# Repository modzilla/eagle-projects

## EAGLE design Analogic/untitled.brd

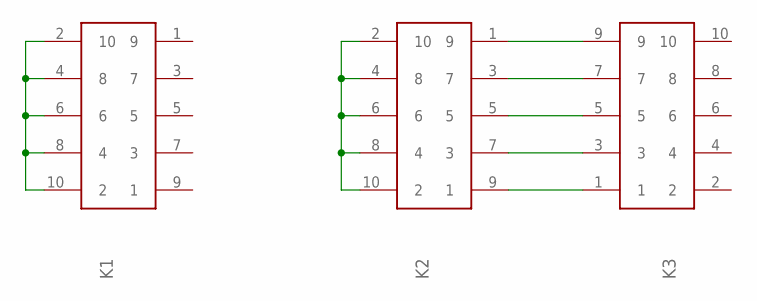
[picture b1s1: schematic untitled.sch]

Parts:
K1, K2: 61201021721
K3: 612X1020621

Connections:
unnamed: K2.9 (1), K3.1
unnamed: K2.7 (3), K3.3
unnamed: K2.5, K3.5
unnamed: K2.3 (7), K3.7
unnamed: K2.1 (9), K3.9
unnamed: K2.2 (10), K2.4 (8), K2.6, K2.8 (4), K2.10 (2)
unnamed: K1.2 (10), K1.4 (8), K1.6, K1.8 (4), K1.10 (2)

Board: 2 copper layers, 3 parts (0 on the bottom side), 7 nets, no tracks yet.

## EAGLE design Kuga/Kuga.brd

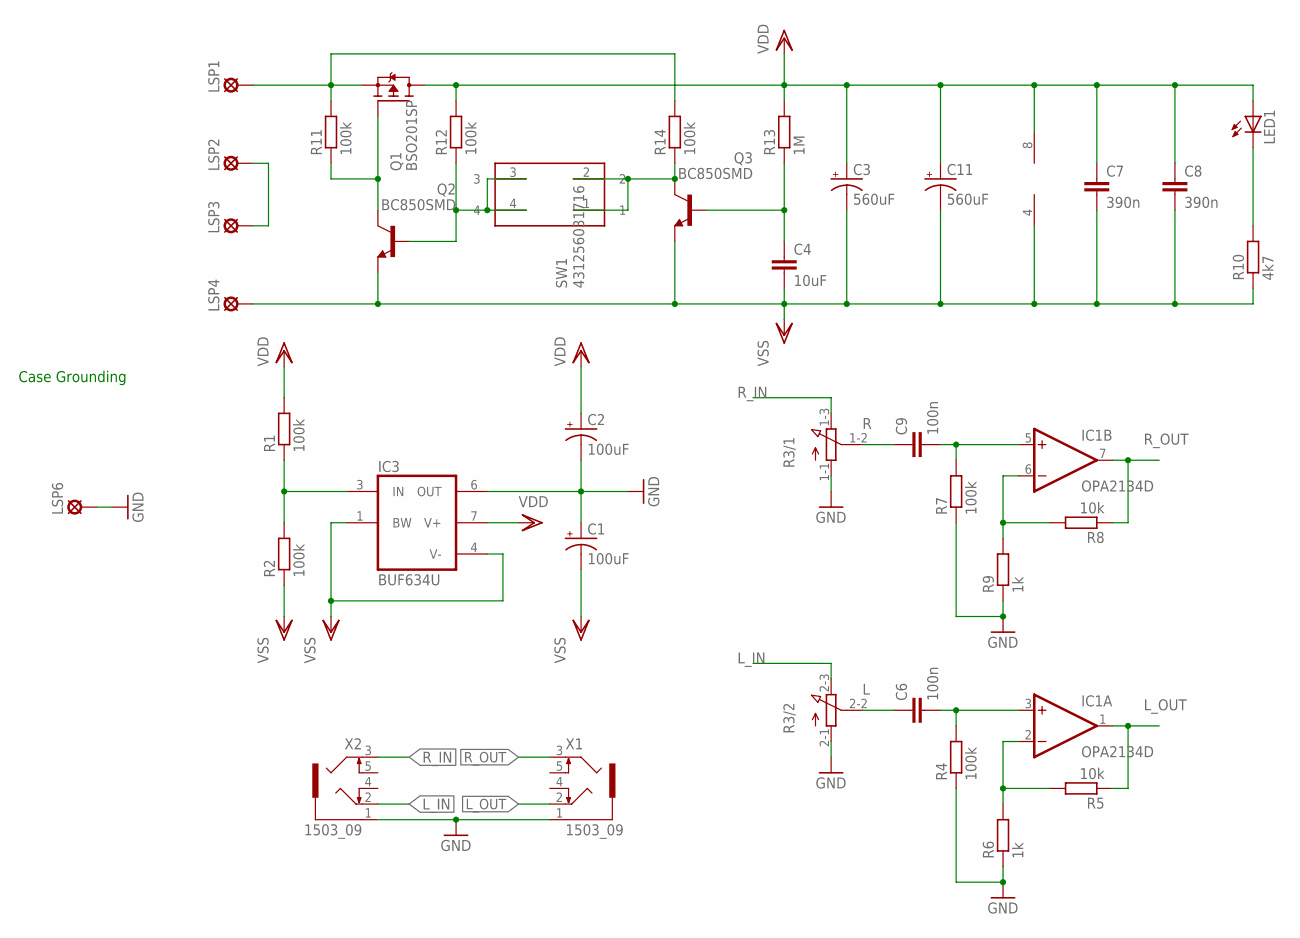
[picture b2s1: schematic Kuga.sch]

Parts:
C1, C2: 100uF; PANASONIC_D
C3, C11: 560uF; PANASONIC_G
C4: 10uF; 1210
C6, C9: 100n; C1206
C7, C8: 390n; C1206
IC1: OPA2134D; SOIC8
IC3: BUF634U; SO08
LED1: LED3MM
LSP1, LSP2, LSP3, LSP4, LSP6: LSP10
Q1: BSO201SP; SO-8
Q2, Q3: BC850SMD; SOT23-BEC
R1, R2, R4, R7, R11, R12, R14: 100k; R1206
R3: 3RP/1610G
R5, R8: 10k; R1206
R6, R9: 1k; R1206
R10: 4k7; R1206
R13: 1M; R1206
SW1: 431256031716
X1, X2: 1503_09

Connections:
GND: C1.+, C2.-, IC3.6 (OUT), LSP6.MP, R3.1-1 (A), R3.2-1 (A), R4.1, R6.1, R7.1, R9.1, X1.1, X2.1
L: C6.1, R3.2-2 (S)
L_IN: R3.2-3 (E), X2.2
L_OUT: IC1.1 (OUT), R5.1, X1.2
unnamed: LED1.K (C), R10.2
unnamed: C6.2, IC1.3 (+IN), R4.2
unnamed: IC1.2 (-IN), R5.2, R6.2
unnamed: C9.2, IC1.5 (+IN), R7.2
unnamed: IC3.3 (IN), R1.1, R2.2
unnamed: IC1.6 (-IN), R8.2, R9.2
unnamed: LSP1.MP, Q1.1 (S), Q1.2 (S), Q1.3 (S), R11.2, R14.2
unnamed: Q2.B, R12.1, SW1.3, SW1.4
unnamed: Q1.4 (G), Q2.C, R11.1
unnamed: C4.1, Q3.B, R13.1
unnamed: Q3.C, R14.1, SW1.1, SW1.2
R: C9.1, R3.1-2 (S)
R_IN: R3.1-3 (E), X2.3
R_OUT: IC1.7 (OUT), R8.1, X1.3
VDD: C2.+, C3.+, C7.1, C8.1, C11.+, IC1.8 (V+), IC3.7 (V+), LED1.A, Q1.5 (D), Q1.6 (D), Q1.7 (D), Q1.8 (D), R1.2, R12.2, R13.2
VSS: C1.-, C3.-, C4.2, C7.2, C8.2, C11.-, IC1.4 (V-), IC3.1 (BW), IC3.4 (V-), LSP4.MP, Q2.E, Q3.E, R2.1, R10.1
~BAT: LSP2.MP, LSP3.MP

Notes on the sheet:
Case Grounding

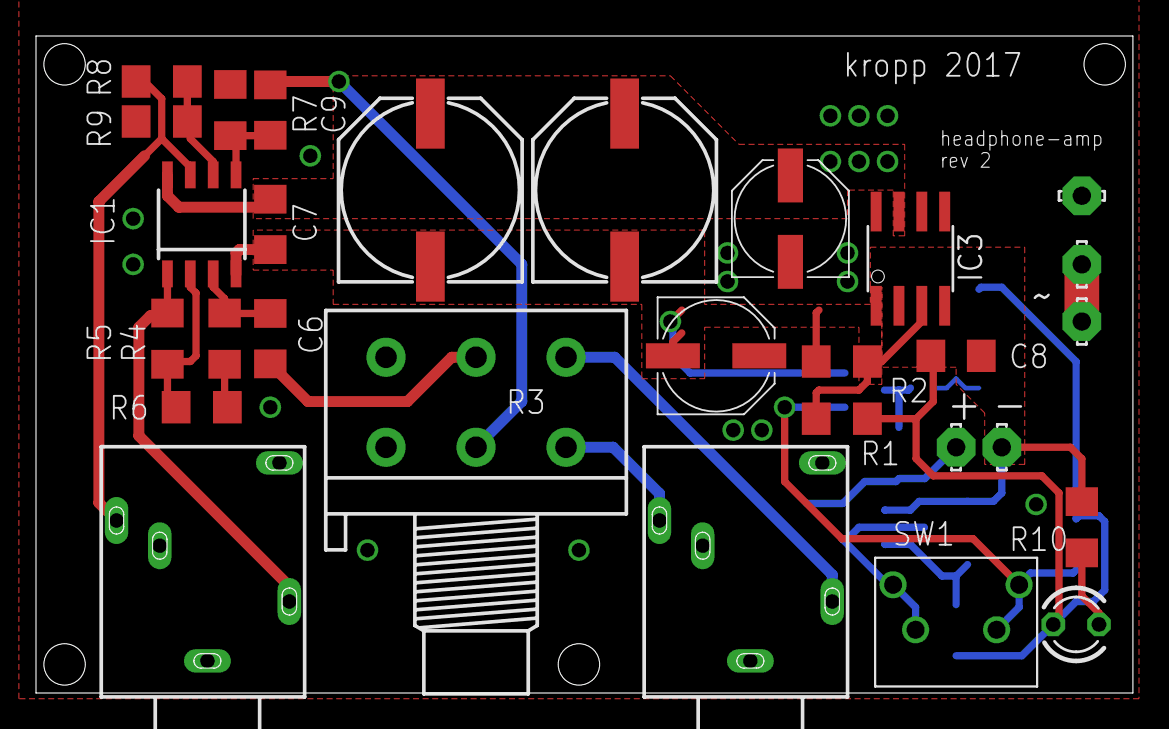
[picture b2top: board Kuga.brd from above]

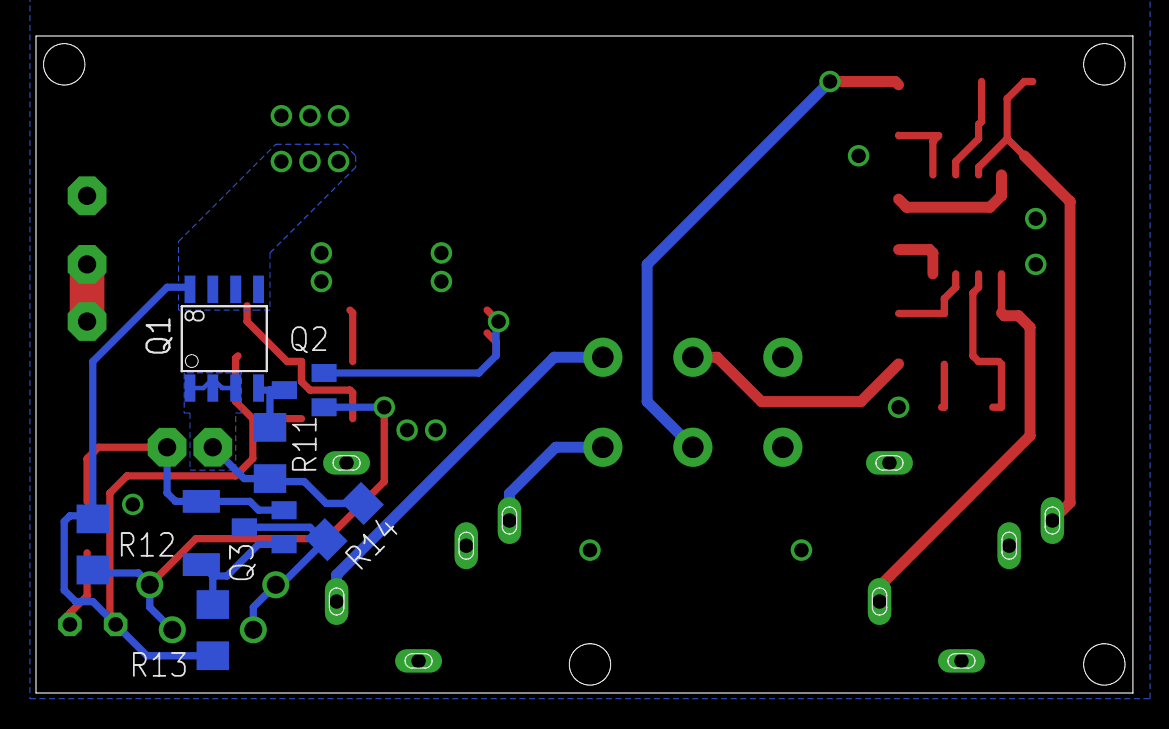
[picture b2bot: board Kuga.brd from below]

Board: 2 copper layers, 60.9 x 36.5 mm, 37 parts (8 on the bottom side), 21 nets.

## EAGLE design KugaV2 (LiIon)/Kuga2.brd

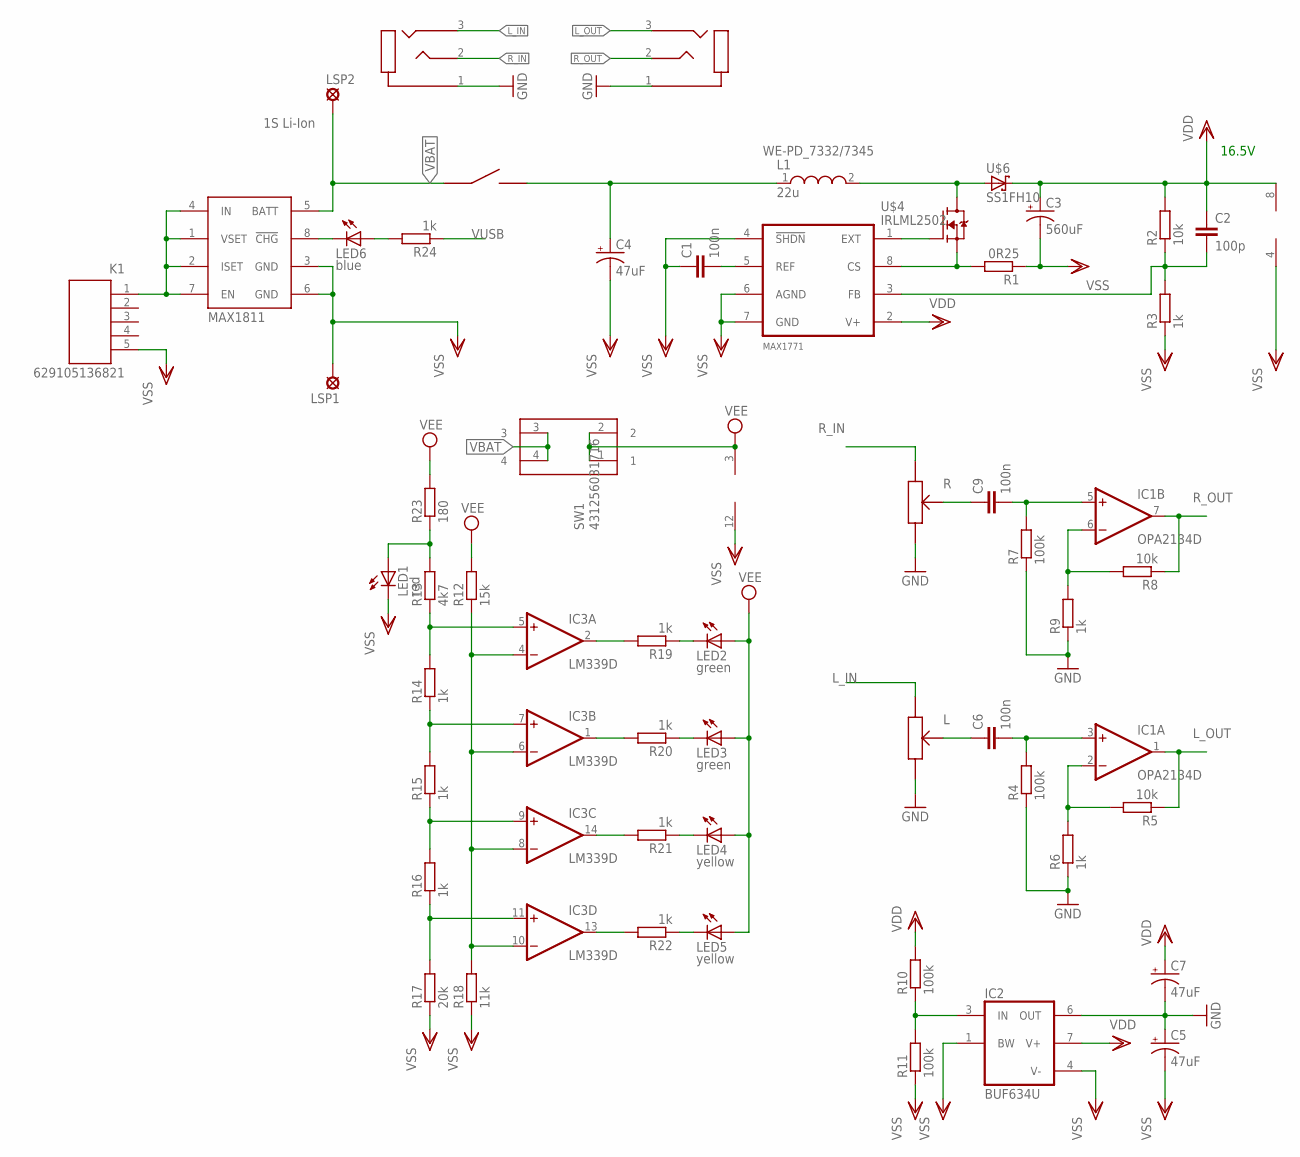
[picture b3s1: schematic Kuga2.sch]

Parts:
C1: 100n; C0603K
C2: 100p; C0603
C3: 560uF; PANASONIC_G
C4, C5, C7: 47uF; PANASONIC_D
C6, C9: 100n; C1206
IC1: OPA2134D; SOIC8
IC2: BUF634U; SO08
IC3: LM339D; SO14
K1: 629105136821
L1: 22u; WE-PD_7332/7345
LED1: red; CHIP-LED0603
LED2, LED3: green; CHIP-LED0603
LED4, LED5: yellow; CHIP-LED0603
LED6: blue; CHIP-LED0603
LSP1, LSP2: LSP10
MAX1771: MAX1771; SO-08
MAX1811: MAX1811; SO-08
R1: 0R25; M3216
R2: 10k; R0603
R3, R14, R15, R16, R19, R20, R21, R22, R24: 1k; R0603
R4, R7: 100k; R1206
R5, R8: 10k; R1206
R6, R9: 1k; R1206
R10, R11: 100k; R0603
R12: 15k; R0603
R13: 4k7; R0603
R17: 20k; R0603
R18: 11k; R0603
R23: 180; R0603
SW1: 431256031716
U$1, U$2: SJ1-3515-SMT-TR; STX-35332-3N-TR
U$4: IRLML2502; SOT23
U$5: PTR90; PTR902
U$6: SS1FH10; DO-219AB

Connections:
GND: C5.+, C7.-, IC2.6 (OUT), R4.1, R6.1, R7.1, R9.1, U$1.1 (SLEEVE), U$2.1 (SLEEVE), U$5.R13 (13), U$5.R23 (13)
L: C6.1, U$5.R22 (12)
L_IN: U$2.3 (RING), U$5.R21 (11)
L_OUT: IC1.1 (OUT), R5.1, U$1.3 (RING)
unnamed: IC2.3 (IN), R10.1, R11.2
unnamed: C6.2, IC1.3 (+IN), R4.2
unnamed: IC1.2 (-IN), R5.2, R6.2
unnamed: C9.2, IC1.5 (+IN), R7.2
unnamed: MAX1771.8 (CS), R1.2, U$4.2 (S)
unnamed: IC1.6 (-IN), R8.2, R9.2
unnamed: MAX1771.1 (EXT), U$4.1 (G)
unnamed: L1.2, U$4.3 (D), U$6.A
unnamed: LED6.C, MAX1811.8 (!CHG)
unnamed: LED6.A, R24.2
unnamed: IC3.4 (-IN), IC3.6 (-IN), IC3.8 (-IN), IC3.10 (-IN), R12.1, R18.2
unnamed: C2.2, MAX1771.3 (FB), R2.1, R3.2
unnamed: IC3.5 (+IN), R13.1, R14.2
unnamed: C1.2, MAX1771.5 (REF)
unnamed: IC3.7 (+IN), R14.1, R15.2
unnamed: IC3.11 (+IN), R16.1, R17.2
unnamed: IC3.9 (+IN), R15.1, R16.2
unnamed: IC3.2 (OUT), R19.2
unnamed: IC3.1 (OUT), R20.2
unnamed: IC3.14 (OUT), R21.2
unnamed: IC3.13 (OUT), R22.2
unnamed: LED2.C, R19.1
unnamed: LED3.C, R20.1
unnamed: LED4.C, R21.1
unnamed: LED5.C, R22.1
unnamed: LED1.A, R13.2, R23.1
R: C9.1, U$5.R12 (12)
R_IN: U$2.2 (TIP), U$5.R11 (11)
R_OUT: IC1.7 (OUT), R8.1, U$1.2 (TIP)
VBAT: LSP2.MP, MAX1811.5 (BATT), SW1.3, SW1.4, U$5.SW1 (11)
VBATSW: C4.+, L1.1, U$5.SW2 (12)
VDD: C2.1, C3.+, C7.+, IC1.8 (V+), IC2.7 (V+), MAX1771.2 (V+), R2.2, R10.2, U$6.K (C)
VEE: IC3.3 (V+), LED2.A, LED3.A, LED4.A, LED5.A, R12.2, R23.2, SW1.1, SW1.2
VSS: C1.1, C3.-, C4.-, C5.-, IC1.4 (V-), IC2.1 (BW), IC2.4 (V-), IC3.12 (GND), K1.5, LED1.C, LSP1.MP, MAX1771.4 (!SHDN), MAX1771.6 (AGND), MAX1771.7 (GND), MAX1811.3 (GND), MAX1811.6 (GND), R1.1, R3.1, R11.1, R17.1, R18.1
VUSB: K1.1, MAX1811.1 (VSET), MAX1811.2 (ISET), MAX1811.4 (IN), MAX1811.7 (EN), R24.1

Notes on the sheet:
16.5V
1S Li-Ion
WE-PD_7332/7345

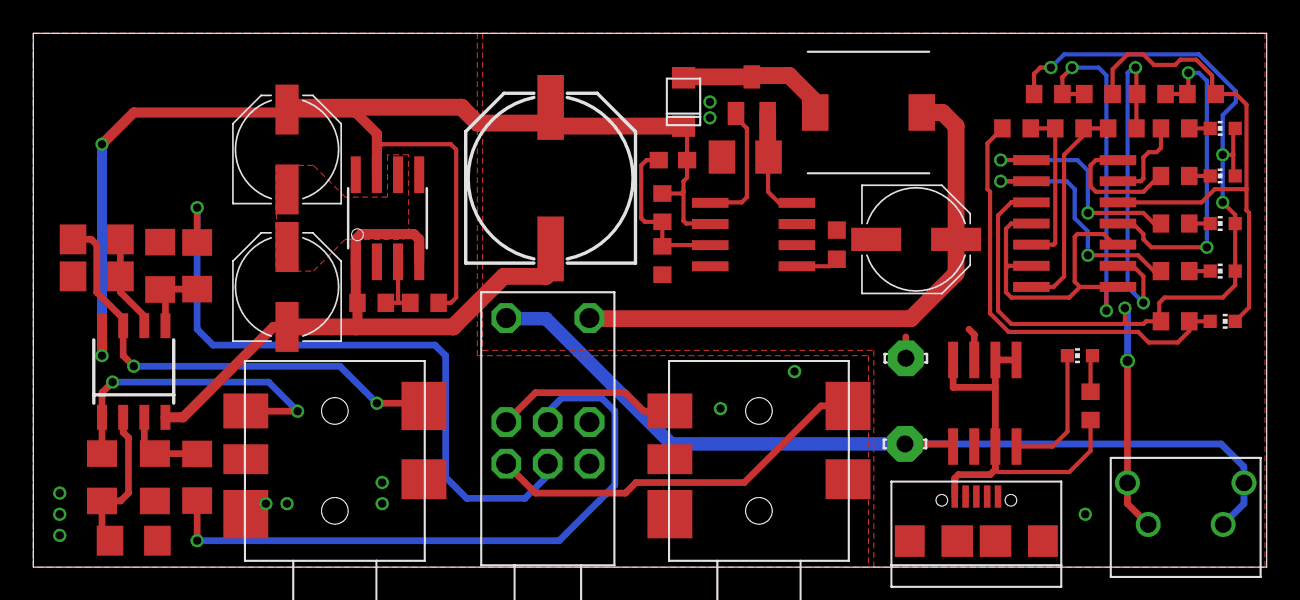
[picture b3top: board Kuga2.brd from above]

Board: 2 copper layers, 74.1 x 32.1 mm, 53 parts (0 on the bottom side), 39 nets.

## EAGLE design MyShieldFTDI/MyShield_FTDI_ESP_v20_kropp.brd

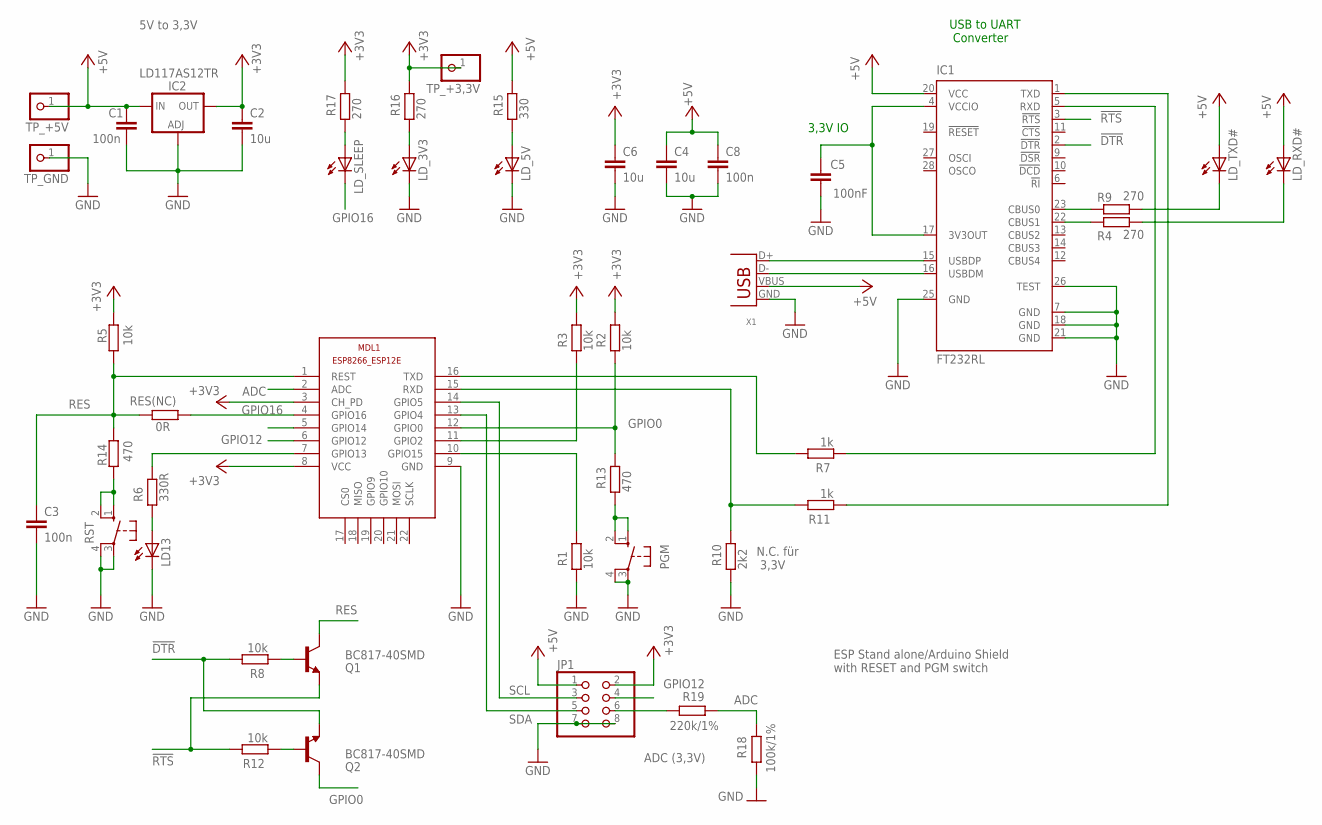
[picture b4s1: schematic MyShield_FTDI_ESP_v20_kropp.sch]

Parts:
C1, C3, C8: 100n; C1206
C2, C4, C6: 10u; C1206
C5: 100nF; C1206
IC1: FT232RL; SSOP28
IC2: LD117AS12TR; SOT223
JP1: PINHD-2X4; 2X04
LD13: LEDSMT1206; 1206
LD_3V3, LD_5V: LEDSMT1206; 1206
LD_RXD#: LEDSMT1206; 1206
LD_SLEEP: LEDSMT1206; 1206
LD_TXD#: LEDSMT1206; 1206
MDL1: ESP8266-12EESP8266-ESP12E; ESP8266-ESP12E
PGM: 10-XX; B3F-10XX
Q1, Q2: BC817-40SMD; SOT23-BEC
R1, R2, R3, R5, R8, R12: 10k; R1206
R4, R9, R16, R17: 270; R1206
R6: 330R; R1206
R7, R11: 1k; R1206
R10: 2k2; R1206
R13, R14: 470; R1206
R15: 330; R1206
R18: 100k/1%; R1206
R19: 220k/1%; R1206
RES(NC): 0R; R0805
RST: 10-XX; B3F-10XX
TP_+3,3V, TP_+5V: PINHD-1X1; 1X01
TP_GND: PINHD-1X1; 1X01
X1: USB-A-S

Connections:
3V3OUT: C5.2, IC1.4 (VCCIO), IC1.17 (3V3OUT)
!DTR: IC1.2 (!DTR), Q2.E, R8.2
!RTS: IC1.3 (!RTS), Q1.E, R12.2
+3V3: C2.1, C6.1, IC2.4 (OUT), JP1.2, MDL1.3 (CH_PD), MDL1.8 (VCC), R2.2, R3.2, R5.1, R16.2, R17.2, TP_+3,3V.1
+5V: C1.1, C4.1, C8.1, IC1.20 (VCC), IC2.3 (IN), JP1.1, LD_RXD#.A, LD_TXD#.A, R15.2, TP_+5V.1, X1.VBUS
ADC: MDL1.2 (ADC), R18.1, R19.2
GND: C1.2, C2.2, C3.2, C4.2, C5.1, C6.2, C8.2, IC1.7 (GND), IC1.18 (GND), IC1.21 (GND), IC1.25 (GND), IC1.26 (TEST), IC2.1 (ADJ), JP1.7, JP1.8, LD13.C, LD_3V3.C, LD_5V.C, MDL1.9 (GND), PGM.3, PGM.4 (P1), R1.1, R10.1, R18.2, RST.3, RST.4 (P1), TP_GND.1, X1.GND
GPIO0: MDL1.12 (GPIO0), Q2.C, R2.1, R13.2
GPIO12: JP1.4, MDL1.6 (GPIO12)
GPIO16: LD_SLEEP.C, MDL1.4 (GPIO16), RES(NC).1
unnamed: MDL1.7 (GPIO13), R6.1
unnamed: LD13.A, R6.2
unnamed: LD_TXD#.C, R9.2
unnamed: LD_RXD#.C, R4.2
unnamed: IC1.23 (CBUS0), R9.1
unnamed: IC1.22 (CBUS1), R4.1
unnamed: IC1.16 (USBDM), X1.D-
unnamed: JP1.6, R19.1
unnamed: Q1.B, R8.1
unnamed: IC1.15 (USBDP), X1.D+
unnamed: LD_SLEEP.A, R17.1
unnamed: MDL1.10 (GPIO15), R1.2
unnamed: MDL1.11 (GPIO2), R3.1
unnamed: Q2.B, R12.1
unnamed: PGM.1 (S), PGM.2 (S1), R13.1
unnamed: R14.2, RST.1 (S), RST.2 (S1)
unnamed: LD_3V3.A, R16.1
unnamed: LD_5V.A, R15.1
RES: C3.1, MDL1.1 (REST), Q1.C, R5.2, R14.1, RES(NC).2
RX_UA: IC1.5 (RXD), R7.1
RX_UA2: MDL1.16 (TXD), R7.2
SCL: JP1.3, MDL1.14 (GPIO5)
SDA: JP1.5, MDL1.13 (GPIO4)
TX_UA: IC1.1 (TXD), R11.1
TX_UA2: MDL1.15 (RXD), R10.2, R11.2

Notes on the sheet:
5V to 3,3V
ESP Stand alone/Arduino Shield with RESET and PGM switch
3,3V IO
USB to UART Converter
N.C. für 3,3V
ADC (3,3V)

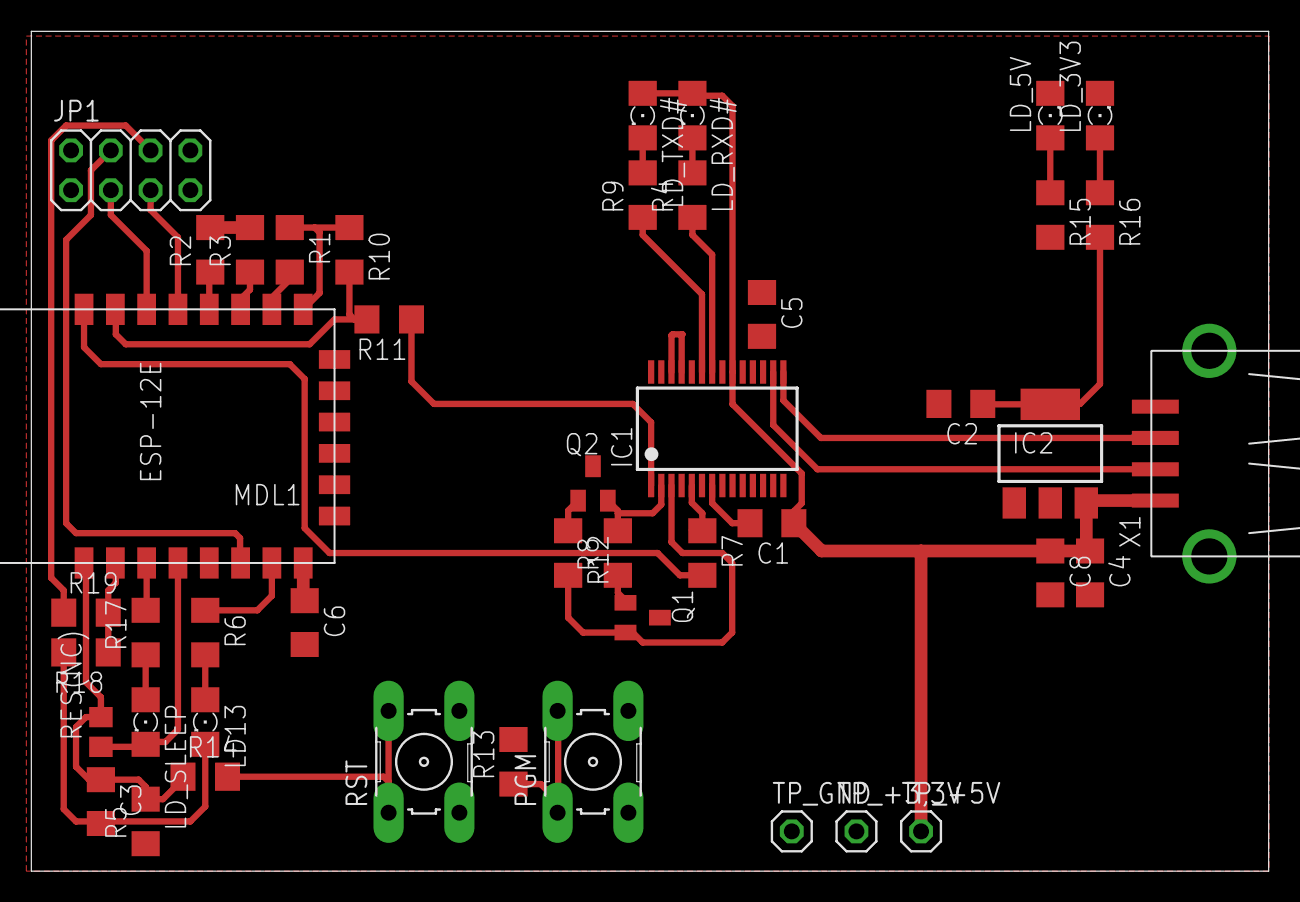
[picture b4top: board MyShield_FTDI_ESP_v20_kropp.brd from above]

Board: 2 copper layers, 79.0 x 53.6 mm, 45 parts (0 on the bottom side), 35 nets.

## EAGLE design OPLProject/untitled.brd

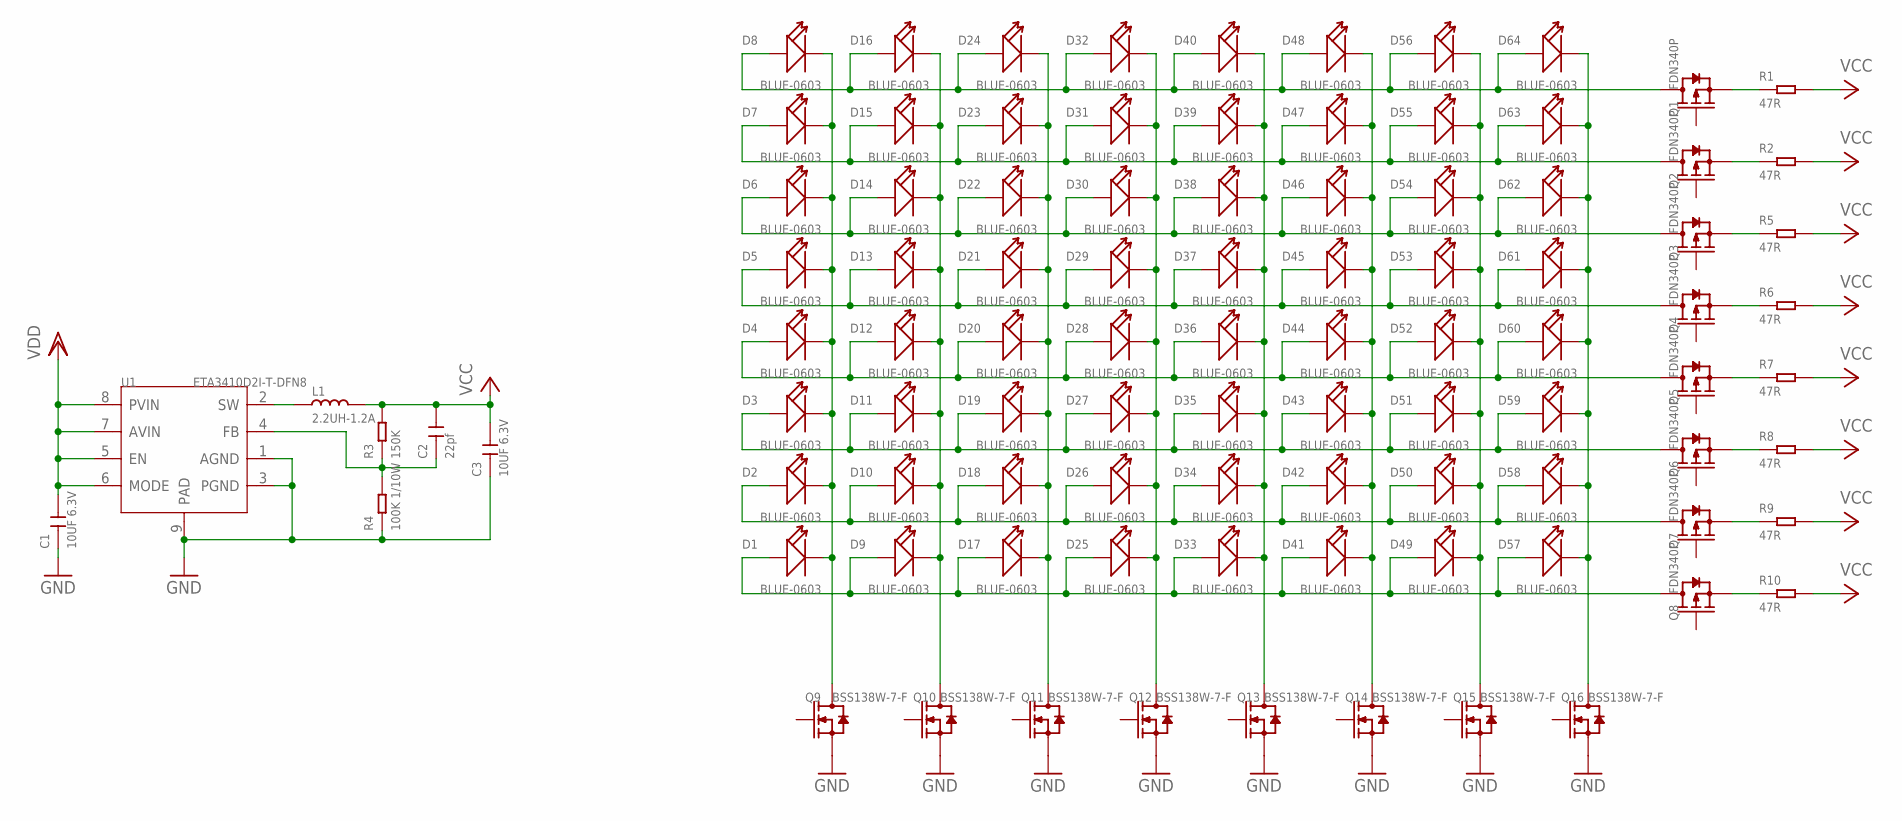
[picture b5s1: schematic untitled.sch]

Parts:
C1, C3: 10UF 6.3V; C0603
C2: 22pf; C0603
D1, D2, D3, D4, D5, D6, D7, D8, D9, D10, D11, D12, D13, D14, D15, D16, D17, D18, D19, D20, D21, D22, D23, D24, D25, D26, D27, D28, D29, D30, D31, D32, D33, D34, D35, D36, D37, D38, D39, D40, D41, D42, D43, D44, D45, D46, D47, D48, D49, D50, D51, D52, D53, D54, D55, D56, D57, D58, D59, D60, D61, D62, D63, D64: BLUE-0603; LED-0603
L1: 2.2UH-1.2A; L0805
Q1, Q2, Q3, Q4, Q5, Q6, Q7, Q8: FDN340P; SOT-23
Q9, Q10, Q11, Q12, Q13, Q14, Q15, Q16: BSS138W-7-F; SOT-23
R1, R2, R5, R6, R7, R8, R9, R10: 47R; PR-D2.3XL6.5MM
R3: 150K; R0603
R4: 100K 1/10W; R0603
U1: ETA3410D2I-T-DFN8; DFN8G-0.5-2X2MM

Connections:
GND: C1.1, C3.1, Q9.2 (S), Q10.2 (S), Q11.2 (S), Q12.2 (S), Q13.2 (S), Q14.2 (S), Q15.2 (S), Q16.2 (S), R4.1, U1.1 (AGND), U1.3 (PGND), U1.9 (PAD)
unnamed: D17.-, D18.-, D19.-, D20.-, D21.-, D22.-, D23.-, D24.-, Q11.3 (D)
unnamed: D2.+, D10.+, D18.+, D26.+, D34.+, D42.+, D50.+, D58.+, Q7.3 (D)
unnamed: D3.+, D11.+, D19.+, D27.+, D35.+, D43.+, D51.+, D59.+, Q6.3 (D)
unnamed: D4.+, D12.+, D20.+, D28.+, D36.+, D44.+, D52.+, D60.+, Q5.3 (D)
unnamed: D5.+, D13.+, D21.+, D29.+, D37.+, D45.+, D53.+, D61.+, Q4.3 (D)
unnamed: D6.+, D14.+, D22.+, D30.+, D38.+, D46.+, D54.+, D62.+, Q3.3 (D)
unnamed: D7.+, D15.+, D23.+, D31.+, D39.+, D47.+, D55.+, D63.+, Q2.3 (D)
unnamed: D8.+, D16.+, D24.+, D32.+, D40.+, D48.+, D56.+, D64.+, Q1.3 (D)
unnamed: D1.+, D9.+, D17.+, D25.+, D33.+, D41.+, D49.+, D57.+, Q8.3 (D)
unnamed: D1.-, D2.-, D3.-, D4.-, D5.-, D6.-, D7.-, D8.-, Q9.3 (D)
unnamed: D9.-, D10.-, D11.-, D12.-, D13.-, D14.-, D15.-, D16.-, Q10.3 (D)
unnamed: D25.-, D26.-, D27.-, D28.-, D29.-, D30.-, D31.-, D32.-, Q12.3 (D)
unnamed: D33.-, D34.-, D35.-, D36.-, D37.-, D38.-, D39.-, D40.-, Q13.3 (D)
unnamed: D41.-, D42.-, D43.-, D44.-, D45.-, D46.-, D47.-, D48.-, Q14.3 (D)
unnamed: D49.-, D50.-, D51.-, D52.-, D53.-, D54.-, D55.-, D56.-, Q15.3 (D)
unnamed: D57.-, D58.-, D59.-, D60.-, D61.-, D62.-, D63.-, D64.-, Q16.3 (D)
unnamed: L1.1, U1.2 (SW)
unnamed: Q1.2 (S), R1.1
unnamed: C2.1, R3.1, R4.2, U1.4 (FB)
unnamed: Q2.2 (S), R2.1
unnamed: Q3.2 (S), R5.1
unnamed: Q4.2 (S), R6.1
unnamed: Q5.2 (S), R7.1
unnamed: Q6.2 (S), R8.1
unnamed: Q7.2 (S), R9.1
unnamed: Q8.2 (S), R10.1
VCC: C2.2, C3.2, L1.2, R1.2, R2.2, R3.2, R5.2, R6.2, R7.2, R8.2, R9.2, R10.2
VDD: C1.2, U1.5 (EN), U1.6 (MODE), U1.7 (AVIN), U1.8 (PVIN)

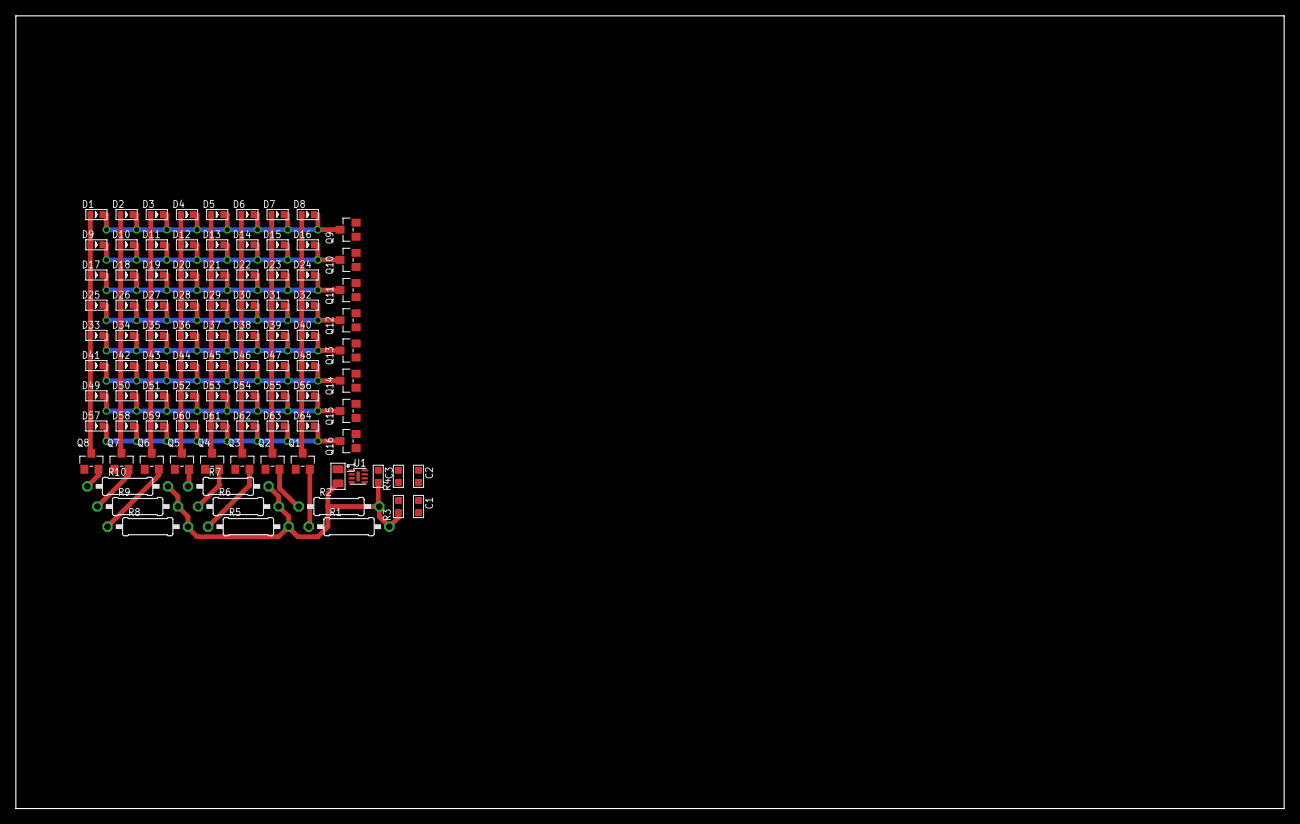
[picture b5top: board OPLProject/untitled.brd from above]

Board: 2 copper layers, 160.0 x 100.0 mm, 95 parts (0 on the bottom side), 29 nets.

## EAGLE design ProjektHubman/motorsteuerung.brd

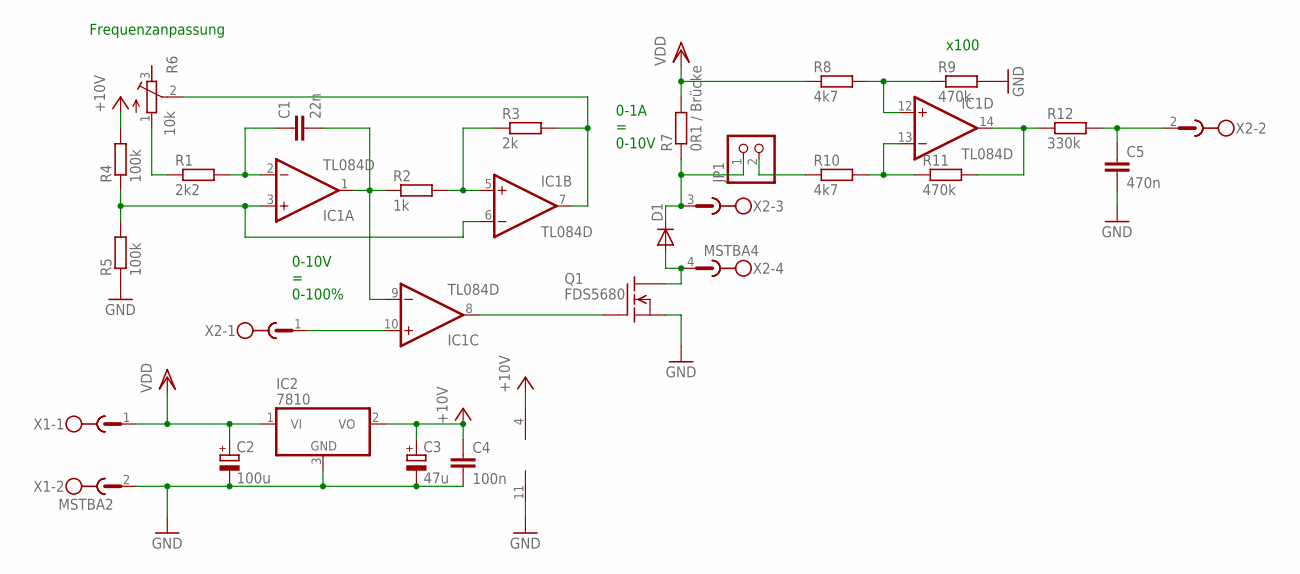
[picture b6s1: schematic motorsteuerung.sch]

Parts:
C1: 22n; C1206
C2: 100u; E3,5-8
C3: 47u; E3,5-8
C4: 100n; C1206
C5: 470n; C1206
D1: 1N4148DO35-7; DO35-7
IC1: TL084D; SO14
IC2: 7810; TO252
JP1: PINHD-1X2; 1X02
Q1: FDS5680; SO-8
R1: 2k2; R1206
R2: 1k; R1206
R3: 2k; R1206
R4, R5: 100k; R1206
R6: 10k; RTRIM4G/J
R7: 0R1 / Brücke; R2512
R8, R10: 4k7; R1206
R9, R11: 470k; R1206
R12: 330k; R1206
X1: MSTBA2
X2: MSTBA4

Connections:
GND: C2.-, C3.-, C4.2, C5.2, IC1.11 (V-), IC2.3 (GND), Q1.1 (S), Q1.2 (S), Q1.3 (S), R5.1, R9.2, X1.2
unnamed: C1.1, IC1.2 (-IN), R1.2
unnamed: C1.2, IC1.1 (OUT), IC1.9 (-IN), R2.1
unnamed: IC1.3 (+IN), IC1.6 (-IN), R4.1, R5.2
unnamed: D1.A, Q1.5 (D), Q1.6 (D), Q1.7 (D), Q1.8 (D), X2.4
unnamed: IC1.5 (+IN), R2.2, R3.1
unnamed: IC1.7 (OUT), R3.2, R6.2 (S)
unnamed: IC1.10 (+IN), X2.1
unnamed: IC1.8 (OUT), Q1.4 (G)
unnamed: R1.1, R6.1 (A)
unnamed: JP1.2, R10.1
unnamed: D1.C, JP1.1, R7.1, X2.3
unnamed: IC1.12 (+IN), R8.2, R9.1
unnamed: IC1.13 (-IN), R10.2, R11.1
unnamed: IC1.14 (OUT), R11.2, R12.1
unnamed: C5.1, R12.2, X2.2
VCC: C3.+, C4.1, IC1.4 (V+), IC2.2 (VO), R4.2
VDD: C2.+, IC2.1 (VI), R7.2, R8.1, X1.1

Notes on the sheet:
0-1A = 0-10V
x100
0-10V = 0-100%
Frequenzanpassung

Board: 2 copper layers, 24 parts (0 on the bottom side), 18 nets, no tracks yet.

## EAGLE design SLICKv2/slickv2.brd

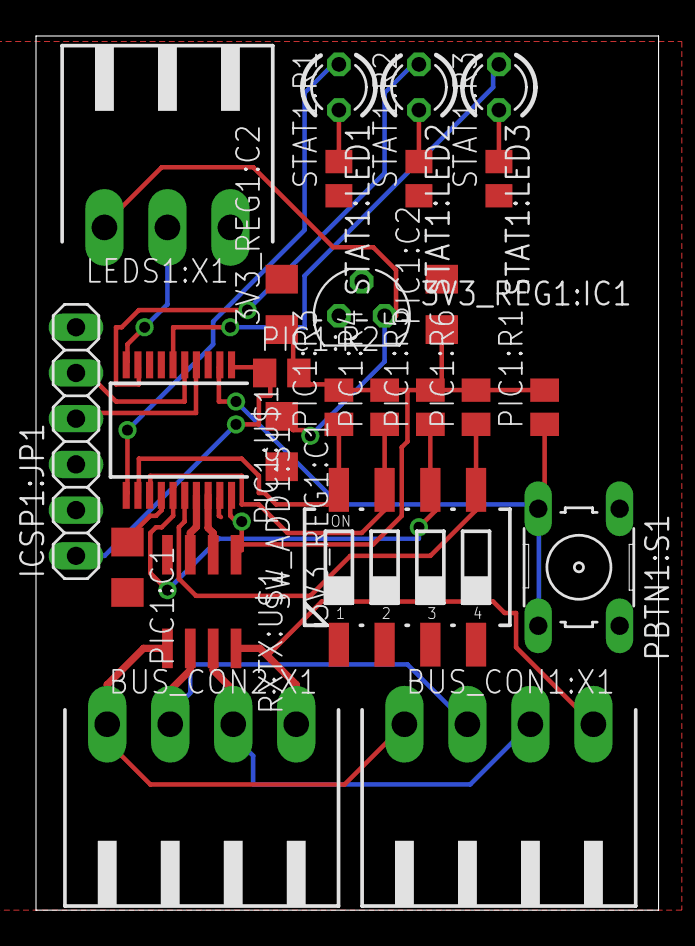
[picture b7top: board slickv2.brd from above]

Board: 2 copper layers, 34.6 x 48.6 mm, 25 parts (0 on the bottom side), 25 nets.

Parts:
3V3_REG1:C1, 3V3_REG1:C2: 100n; C1206
3V3_REG1:IC1: LP2950ACZ-3.3; TO92
BUS_CON1:X1, BUS_CON2:X1: 90G-4
ICSP1:JP1: 1X06
LEDS1:X1: 90G-3
PBTN1:S1: B3F-10XX
PIC1:C1: 10u; C1206
PIC1:C2: 100n; C1206
PIC1:R1, PIC1:R2, PIC1:R3, PIC1:R4, PIC1:R5, PIC1:R6: 10k; M0805
PIC1:U$1: PIC32MM0016GPL020; SSOP20
RXTX:U$1: SN65HVD51; SO-08
STAT1:LED1: GRN; LED3MM
STAT1:LED2: BLU; LED3MM
STAT1:LED3: RED; LED3MM
STAT1:R1, STAT1:R2, STAT1:R3: R0805
SW_ADD1:S1: 219-04; CTS-219-04

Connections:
+3V3: 3V3_REG1:C2.1, 3V3_REG1:IC1.1, ICSP1:JP1.2, PIC1:C2.1, PIC1:R1.2, PIC1:R2.2, PIC1:R3.2, PIC1:R4.2, PIC1:R5.2, PIC1:R6.2, PIC1:U$1.20, RXTX:U$1.1
+5V: 3V3_REG1:C1.1, 3V3_REG1:IC1.3, LEDS1:X1.3
COM0: BUS_CON1:X1.4, BUS_CON2:X1.4, RXTX:U$1.8
COM1: BUS_CON1:X1.3, BUS_CON2:X1.3, RXTX:U$1.7
COM2: BUS_CON1:X1.2, BUS_CON2:X1.2, RXTX:U$1.6
COM3: BUS_CON1:X1.1, BUS_CON2:X1.1, RXTX:U$1.5
GND: 3V3_REG1:C1.2, 3V3_REG1:C2.2, 3V3_REG1:IC1.2, ICSP1:JP1.3, LEDS1:X1.1, PBTN1:S1.1, PBTN1:S1.2, PIC1:C1.2, PIC1:C2.2, PIC1:U$1.19, RXTX:U$1.4, STAT1:R1.1, STAT1:R2.1, STAT1:R3.1, SW_ADD1:S1.1, SW_ADD1:S1.2, SW_ADD1:S1.3, SW_ADD1:S1.4
LEDS: LEDS1:X1.2, PIC1:U$1.10
unnamed: PIC1:U$1.18, RXTX:U$1.2
unnamed: PIC1:U$1.17, RXTX:U$1.3
unnamed: PIC1:U$1.11, STAT1:LED1.A
unnamed: PIC1:U$1.9, STAT1:LED2.A
unnamed: PIC1:U$1.6, STAT1:LED3.A
unnamed: ICSP1:JP1.1, PIC1:R2.1, PIC1:U$1.1
unnamed: ICSP1:JP1.5, PIC1:U$1.5
unnamed: ICSP1:JP1.4, PIC1:U$1.4
unnamed: PIC1:R6.1, PIC1:U$1.16, SW_ADD1:S1.5
unnamed: PIC1:R5.1, PIC1:U$1.15, SW_ADD1:S1.6
unnamed: PIC1:R4.1, PIC1:U$1.13, SW_ADD1:S1.7
unnamed: PIC1:R3.1, PIC1:U$1.12, SW_ADD1:S1.8
unnamed: PBTN1:S1.3, PBTN1:S1.4, PIC1:R1.1, PIC1:U$1.2
PIC1:N$6: PIC1:C1.1, PIC1:U$1.14
STAT1:N$1: STAT1:LED1.K, STAT1:R1.2
STAT1:N$2: STAT1:LED2.K, STAT1:R2.2
STAT1:N$3: STAT1:LED3.K, STAT1:R3.2

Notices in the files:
parts and their libraries:
Wire_to_Board_Connectors_rev15d: Copyright: Würth Elektronik
SparkFun-Capacitors: Licensing: Creative Commons ShareAlike 4.0 International - https://creativecommons.org/licenses/by-sa/4.0
